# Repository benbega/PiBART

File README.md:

## Introduction
As a lifelong resident of the Bay Area, I have seen countless BART trains fly by, always giving off their signature high pitched howl as they barrel down the tracks. BART is a very unique urban transportation system, and although it is not the most efficient, I have grown to love riding it between the East Bay and San Francisco. 

The project outlined below is a fully custom model train, based off of the BART system. It was built to showcase skills in multiple facets of electrical engineering, as well as to be a homage to the legendary train.

A brief example of the train running can be seen [here](https://youtu.be/NTuRKBK8t7I)

## System Breakdown
At a high level, this project can be broken down into the following four major subsystems:

 1. Train Electronics
 2. Train Chassis
 3. Track Electronics
 4. Track Design

At the current time of writing, I am working on version 2 of the project, so the subsystem descriptions below will correspond to that version.

### Train Electronics
The train houses the entirety of the electronics it needs to operate autonomously. The main processing is all done on a Raspberry Pi 4B+, that is powered by a Geekworm X728 uninterruptable power supply (UPS) with two 18650 batteries. In order to know where it is located on the tracks, the Raspberry Pi is connected to an RC522 RFID sensor via SPI. The RFID tags are embedded in the tracks, and are manually preset to have "full speed", "slow", or "medium speed" values. After detecting these tags, the RFID sensor communicated back to the Raspberry Pi and the train enters the speed level corresponding to the tag.

In order to control the motor, the Raspberry Pi outputs logic signals to a custom PCB based around the L293D IC. The PCB has six logic inputs, external power input, two motor output terminals, and two status LEDs for debugging. The PCB is fully custom designed in KiCAD and was fabricated by PCBWay. The PCB can officially support up to 1A for each motor channel, but this number could possibly be higher in the future after some testing and possible integrating a cooling solution.

The train operates using a live third rail, which is currently running at 12V DC. Power from the third rail feeds in from two wires mounted on a side bracket (details on the mount can be found in the following section) and into the power delivery PCB and the Raspberry Pi UPS. The power is stepped down from the 12V to 5V with a simple DC-DC converter to match the needed input on the UPS. In the built configuration, the third rail is continually charging the battery cells on the UPS, which in turn power the Raspberry Pi. Since there are no metal tracks to ground the system, there is a hidden "fourth rail" running in the middle of the trackbed. An identical connection is made from the train to this rail in order to ground the system. 

The drivetrain of the train is based around a single DC motor that can be run in the 5-12V range. More about the drivetrain can be found in the *Train Chassis* section below.

### Train Chassis
The train chassis is entirely custom designed, using a mix of OnShape and TinkerCAD depending on the complexity of the parts. All elements of the chassis are 3d printed except for the ball bearings, which were purchased preassembled. The main chassis of the train is a flat plane with cutouts for the gears (more on those later). The top of the chassis features a slide mount for the Raspberry Pi and a vertical mounting bracket for the power delivery PCB, as well as a mount for the DC motor. In order to transfer power from the live third rail, there is a side mounted bracket to guide wires down from the Raspberry Pi and power delivery PCB. An identical mount runs through the gear cutout on the chassis to provide the ground line connections. The bottom of the chassis is reinforced with 3 extra strips of PLA running along the length of the train, while also featuring mounts for the bearings. The two axles are 1/4" diameter and have wheels friction fit on either end. The train wheels are conical in shape, with an exaggerated flange for extra stability on the small scale.

The drivetrain of the system consists of a DC motor with a 10 tooth gear and a 15 tooth gear mounted on the rear axle. A pulley is used to transfer power between the gears. The current gear ratio is still being iterated on, to find the right performance level for the scale.

### Track Electronics
The trackbed electronics are very simple in theory, but are currently difficult to maintain. The live third rail and grounding fourth rail are both 3d printed from PLA, with a layer of conductive copper tape stuck to the top of each. This copper tape preforms good enough for my needs, with about 5 ohms of resistance measured over 20 inches of rail. The downside of using the copper tape to add conductivity to the rails is its general structural weakness. The tape tears very easily, and wears out over time with the wires from the train car rubbing against it. Adding more tape on top of the worn tape can fix these problems, but also sometimes results in a loss of conductivity along the rail.

In order for the train to control itself, RFID tags are laid within the trackbed, between sleeper planks. Standard 13.56MHz RFID tags are used, in order to keep the system lower cost and less complex.

Power is provided to the third rail and grounding rail at one end of the trackbed, with a standard bench power supply.

### Track Design
The trackbed is a simple 3 rail design, with a small fourth rail running down the center of the tracks. The main rails are spaced with 3.375" between the center of each rail, with the third rail being 1.125" to the right of the trackbed. Each rail segment is 5" in length, and is supported by a sleeper plank at each end. The overall track dimensions were built out after the train chassis was assembled, to ease the design constraints on that part of the project.

## Current Features
The train currently can operate autonomously on a straight section of track, with the third rail running at 12V. A command is issued to the train to start moving initially, and then the Raspberry Pi takes over and controls the train's speed by reading RFID tags, as mentioned above. The train can slow down, speed up, and come to a complete stop autonomously. 

## Future Work
As of September 2023, I am working on optimizing the drivetrain of the system so it runs smoother along the rails. I am currently experimenting with ways of adding grip to the tracks, as well as with ways to better contact the third rail for more consistent power delivery. After these two parts of the system are finished, I will begin experimenting with the train's turn radius to find a suitable dimension to build curved sections of track. I anticipate this will be a longer process, and plan on building out a longer section of straight track simultaneously, to optimize the train control system and find the speed limits of the system. 

### End Notes
I will also be updating this GitHub repo with 3d models, code, images, and more over the coming weeks, so check back periodically if you are interested in the project. 

**I am also looking for work in the electrical engineering field, feel free to reach out if you have any leads.**

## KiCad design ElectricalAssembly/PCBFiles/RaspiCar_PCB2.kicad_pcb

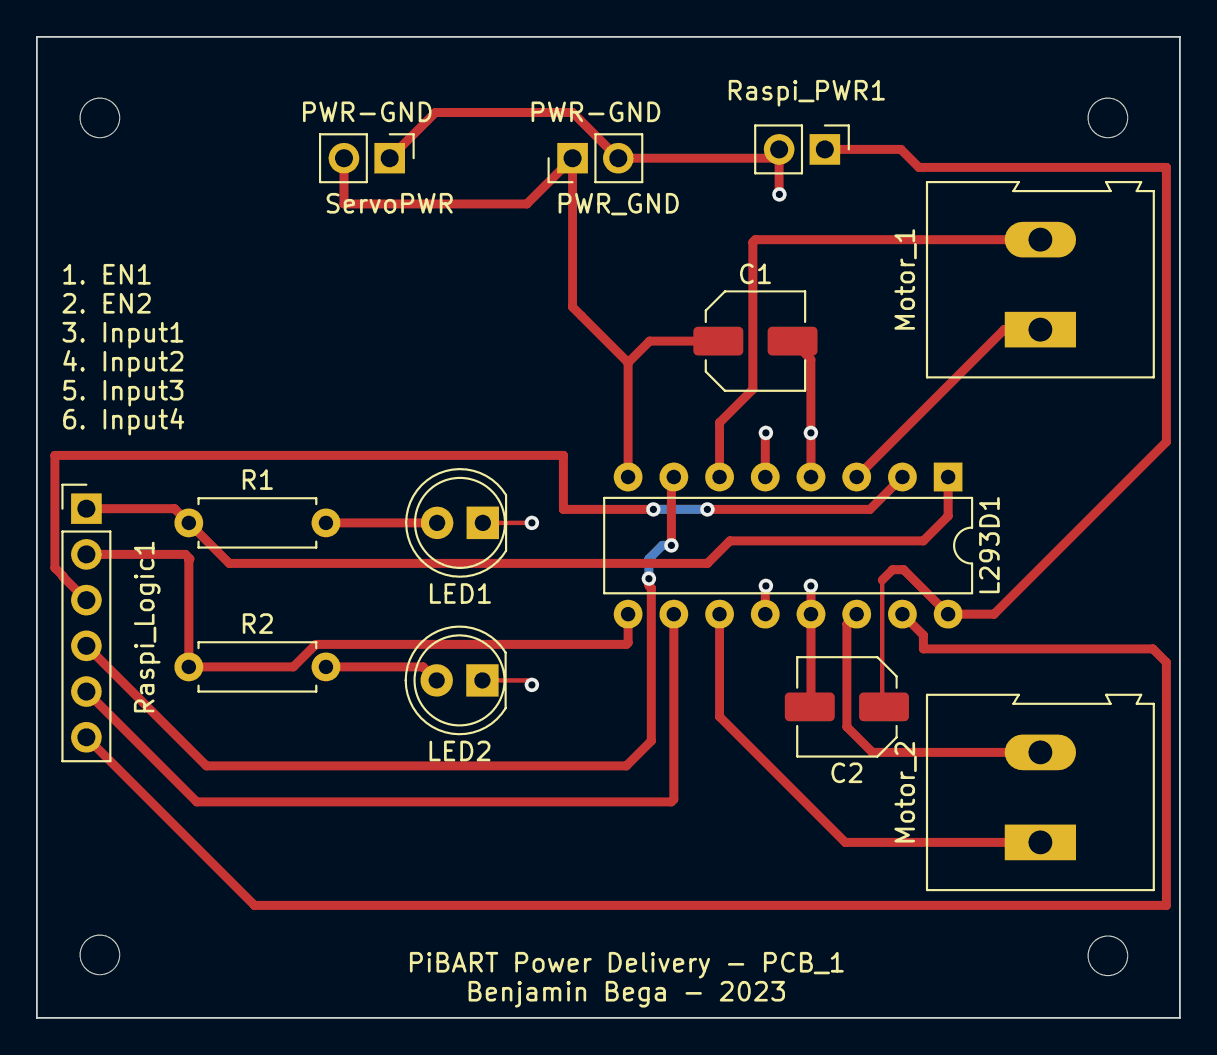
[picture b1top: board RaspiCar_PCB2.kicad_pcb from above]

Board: 2 copper layers, 63.5 x 54.5 mm, 17 parts (0 on the bottom side), 15 nets.

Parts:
C1, C2: 1uF; C_Elec_5x5.4
H1, H2, H3, H4: MountingHole; MountingHole_2.2mm_M2
L293D1: L293D; DIP-16_W7.62mm
LED1: LED1; LED_D5.0mm
LED2: LED2; LED_D5.0mm
Motor_1: MotorTerminal1; TerminalBlock_Altech_AK300-2_P5.00mm
Motor_2: MotorTerminal2; TerminalBlock_Altech_AK300-2_P5.00mm
PWR_GND: PWR_GND; PinHeader_1x02_P2.54mm_Vertical
R1, R2: 3.3k; R_Axial_DIN0207_L6.3mm_D2.5mm_P7.62mm_Horizontal
Raspi_Logic1: PiLogicHeaders; PinHeader_1x06_P2.54mm_Vertical
Raspi_PWR1: RaspiPWR/GND; PinHeader_1x02_P2.54mm_Vertical
ServoPWR: ServoPWR/GND; PinHeader_1x02_P2.54mm_Vertical

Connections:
+5V: C2.1, L293D1.16 (VCC1), Raspi_PWR1.1
+7.5V: C1.1, L293D1.8 (VCC2), PWR_GND.1, ServoPWR.2
GND: C1.2, C2.2, L293D1.4 (GND), L293D1.5 (GND), L293D1.12 (GND), L293D1.13 (GND), LED1.1 (K), LED2.1 (K), PWR_GND.2, Raspi_PWR1.2, ServoPWR.1
unnamed: L293D1.1 (EN1,2), R1.1, Raspi_Logic1.1
unnamed: L293D1.2 (1A), Raspi_Logic1.3
unnamed: L293D1.3 (1Y), Motor_1.1
unnamed: L293D1.6 (2Y), Motor_1.2
unnamed: L293D1.7 (2A), Raspi_Logic1.4
unnamed: L293D1.9 (EN3,4), R2.1, Raspi_Logic1.2
unnamed: L293D1.10 (3A), Raspi_Logic1.5
unnamed: L293D1.11 (3Y), Motor_2.1
unnamed: L293D1.14 (4Y), Motor_2.2
unnamed: L293D1.15 (4A), Raspi_Logic1.6
unnamed: LED1.2 (A), R1.2
unnamed: LED2.2 (A), R2.2

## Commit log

2023-09-29 Added assembly folders
